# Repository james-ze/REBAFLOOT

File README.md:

# REBAFLOOT
Proyecto de Taller de ING Electronica
este es un proyecto creado por estudiantes de ING electronica de la Universidad nacional en la materia de taller. Donde aplicando conceptos de la electronica creamos un robot llamado REBAFLOOT capaz de limpiar la basura que se encuentra flotando en la superficie de ecosistemas maritimos y rios, aqui encontraras todo el procedimiento documentado en un wiki para la elaboracion de este proyecto

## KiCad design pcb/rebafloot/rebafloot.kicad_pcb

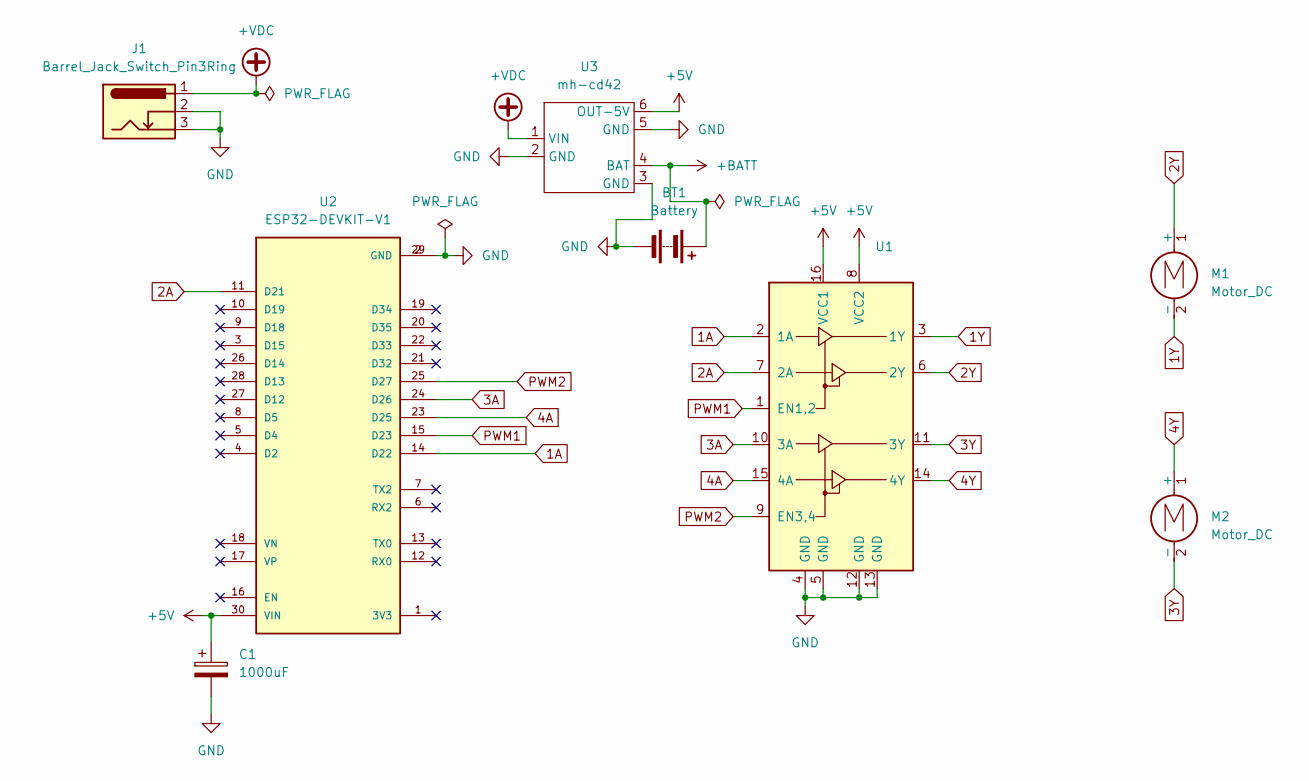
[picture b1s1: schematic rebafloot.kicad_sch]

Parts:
BT1: Battery; PinHeader_1x02_P2.54mm_Vertical
C1: 1000uF; CP_Radial_D13.0mm_P5.00mm
J1: Barrel_Jack_Switch_Pin3Ring; BarrelJack_Horizontal
M1, M2: Motor_DC; PinHeader_1x02_P2.54mm_Vertical
U1: L293D; DIP-16_W7.62mm
U2: ESP32-DEVKIT-V1; MODULE_ESP32_DEVKIT_V1; PARTREV N/A
U3: mh-cd42

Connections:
1A: U1.2 (1A), U2.14 (D22)
1Y: M1.2 (-), U1.3 (1Y)
2A: U1.7 (2A), U2.11 (D21)
2Y: M1.1 (+), U1.6 (2Y)
3A: U1.10 (3A), U2.24 (D26)
3Y: M2.2 (-), U1.11 (3Y)
4A: U1.15 (4A), U2.23 (D25)
4Y: M2.1 (+), U1.14 (4Y)
+5V: C1.1, U1.8 (VCC2), U1.16 (VCC1), U2.30 (VIN), U3.6 (OUT-5V)
+BATT: BT1.1 (+), U3.4 (BAT)
+VDC: J1.1, U3.1 (VIN)
GND: BT1.2 (-), C1.2, J1.2, J1.3, U1.4 (GND), U1.5 (GND), U1.12 (GND), U1.13 (GND), U2.2 (GND), U2.29 (GND), U3.2 (GND), U3.3 (GND), U3.5 (GND)
PWM1: U1.1 (EN1,2), U2.15 (D23)
PWM2: U1.9 (EN3,4), U2.25 (D27)

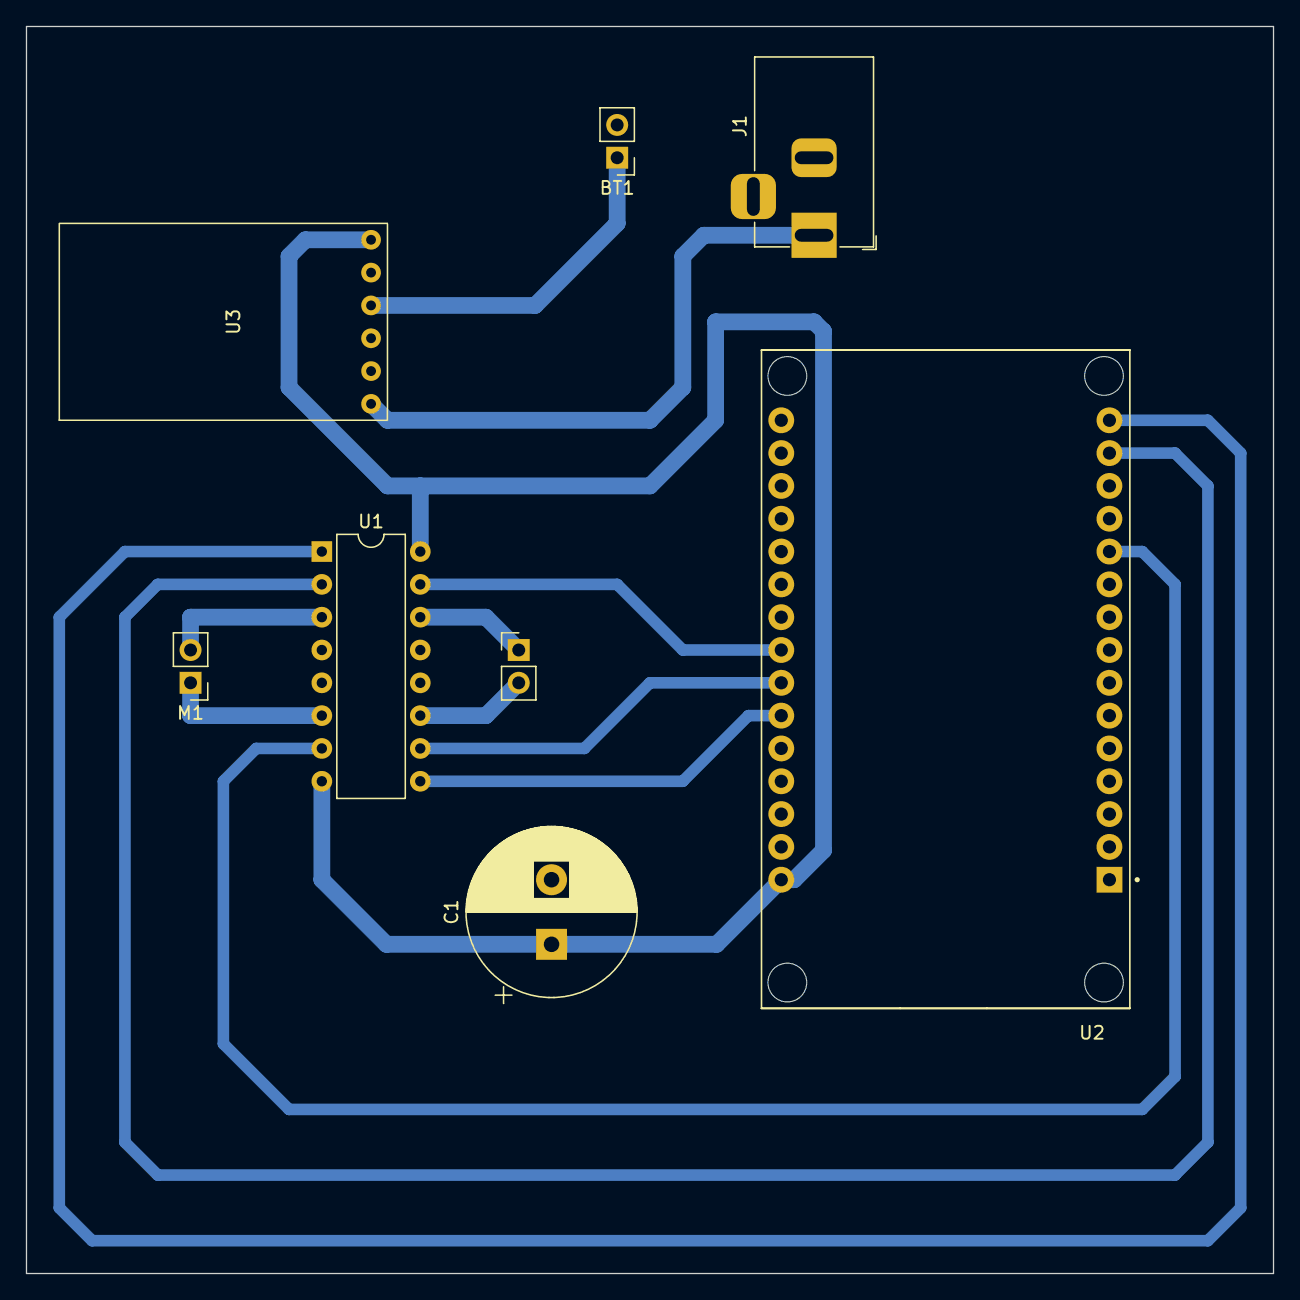
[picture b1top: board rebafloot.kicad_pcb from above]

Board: 2 copper layers, 96.5 x 96.5 mm, 8 parts (0 on the bottom side), 14 nets.

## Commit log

2023-12-01 Create Codigo l29-3d
    Este código sirve para encender los PWM y generar los inputs para las señales que se le entregan al motor
2023-12-01 control remoto_micropython
2023-12-01 Create GitHub - sobre el control
    este Github tiene todo sobre el control de app-inventor
    Propiedad de Jhonny Cubides
2023-12-01 cd-final
2023-12-01 Rename control remoto to codigo control remoto
2023-12-01 Resultado final
2023-12-01 resultado final.jpg
2023-12-01 Create README.md
    descripción breve
